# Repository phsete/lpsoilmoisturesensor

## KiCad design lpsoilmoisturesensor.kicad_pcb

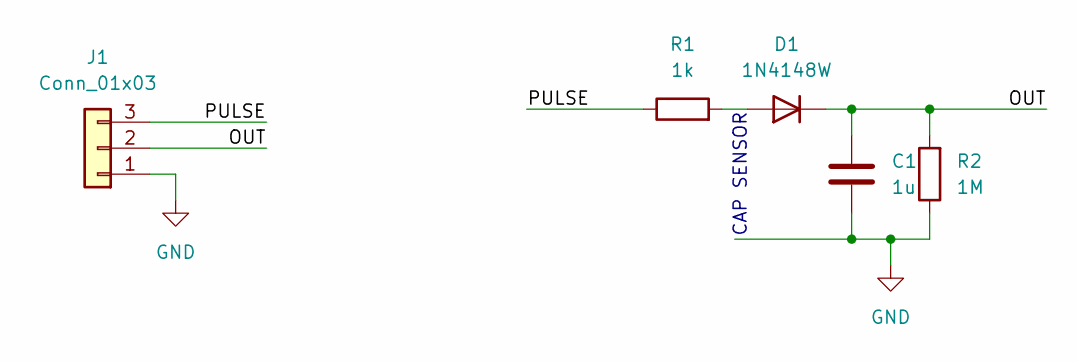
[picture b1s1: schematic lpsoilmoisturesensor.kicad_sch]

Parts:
C1: 1u; C_0805_2012Metric
D1: 1N4148W; D_SOD-123
J1: Conn_01x03; PinHeader_1x03_P2.54mm_Horizontal
R1: 1k; R_0805_2012Metric
R2: 1M; R_0805_2012Metric

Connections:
/OUT: C1.1, D1.1 (K), J1.2, R2.2
/PULSE: J1.3, R1.1
GND: C1.2, J1.1, R2.1
unnamed: D1.2 (A), R1.2

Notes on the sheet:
CAP SENSOR

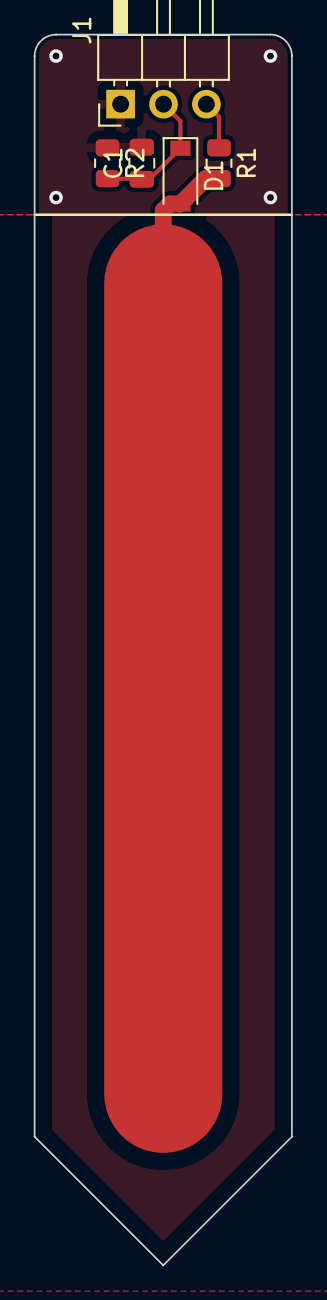
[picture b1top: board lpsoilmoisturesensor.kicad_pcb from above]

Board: 2 copper layers, 15.2 x 72.9 mm, 5 parts (0 on the bottom side), 4 nets.

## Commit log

2023-06-16 rebuild in kicad v6
